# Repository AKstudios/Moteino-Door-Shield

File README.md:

# Moteino Door Shield

This is a door status shield for the Moteino. It uses a reed switch to check the status of a door (open/close). Current draw < 0.1uA
<br><br>

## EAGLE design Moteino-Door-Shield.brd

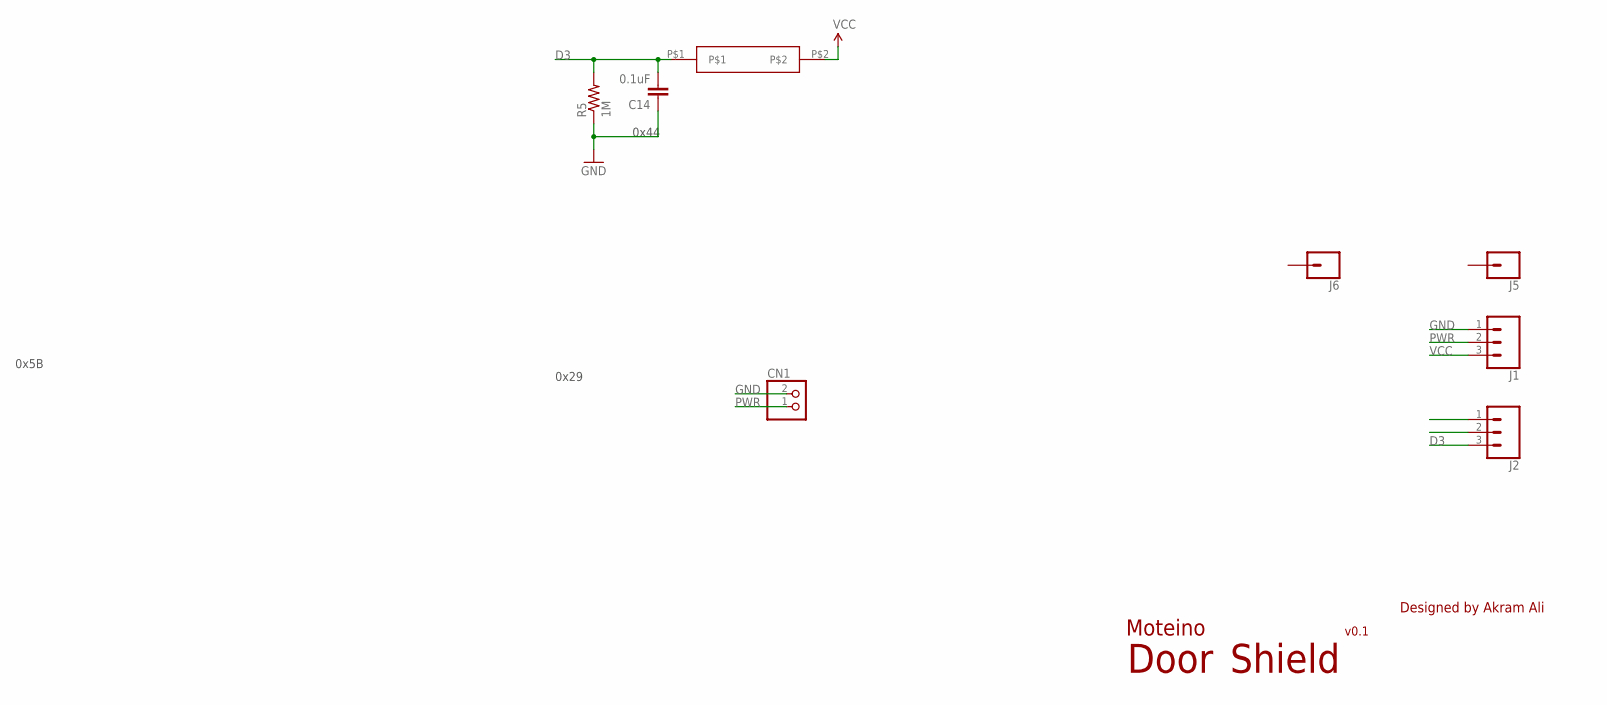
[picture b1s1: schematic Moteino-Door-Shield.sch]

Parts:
C14: 0.1uF; 0805; MPN CC0805KRX7R9BB104
CN1: JST_2PIN-SMT-RA; JST-PH-2-SMT-RA
J1, J2: CONN_03; 1X03
J5, J6: CONN_01; 1X01
R5: 1M; 0805; MPN RC0805FR-0710KL
U$1: SWITCH-REED-SPSPT-NO; SMD

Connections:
D3: C14.2, J2.3, R5.2, U$1.P$1
GND: C14.1, CN1.2 (1), J1.1, R5.1
PWR: CN1.1 (2), J1.2
VCC: J1.3, U$1.P$2

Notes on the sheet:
Moteino
Designed by Akram Ali
Door
0x44
0x29
Shield
v0.1
0x5B

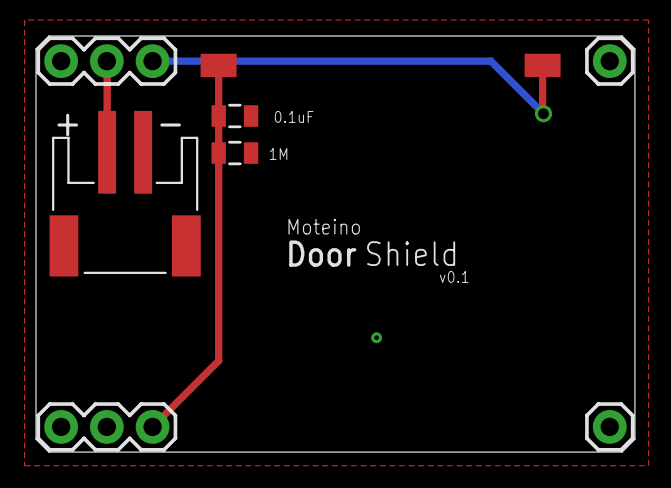
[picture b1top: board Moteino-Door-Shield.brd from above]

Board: 2 copper layers, 33.3 x 23.1 mm, 8 parts (0 on the bottom side), 4 nets.

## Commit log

2017-04-17 :lollipop: Added .gitattributes & .gitignore files
2017-04-17 Added project files
2017-04-17 Updated rendering
2017-04-17 Updated file name
2018-02-19 Added doorshield firmware

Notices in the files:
parts and their libraries:
SparkFun-Connectors: Licensing: CC v3.0 Share-Alike You are welcome to use this library for commercial purposes.
SparkFun-Resistors: Licensing: Creative Commons ShareAlike 4.0 International - https://creativecommons.org/licenses/by-sa/4.0
